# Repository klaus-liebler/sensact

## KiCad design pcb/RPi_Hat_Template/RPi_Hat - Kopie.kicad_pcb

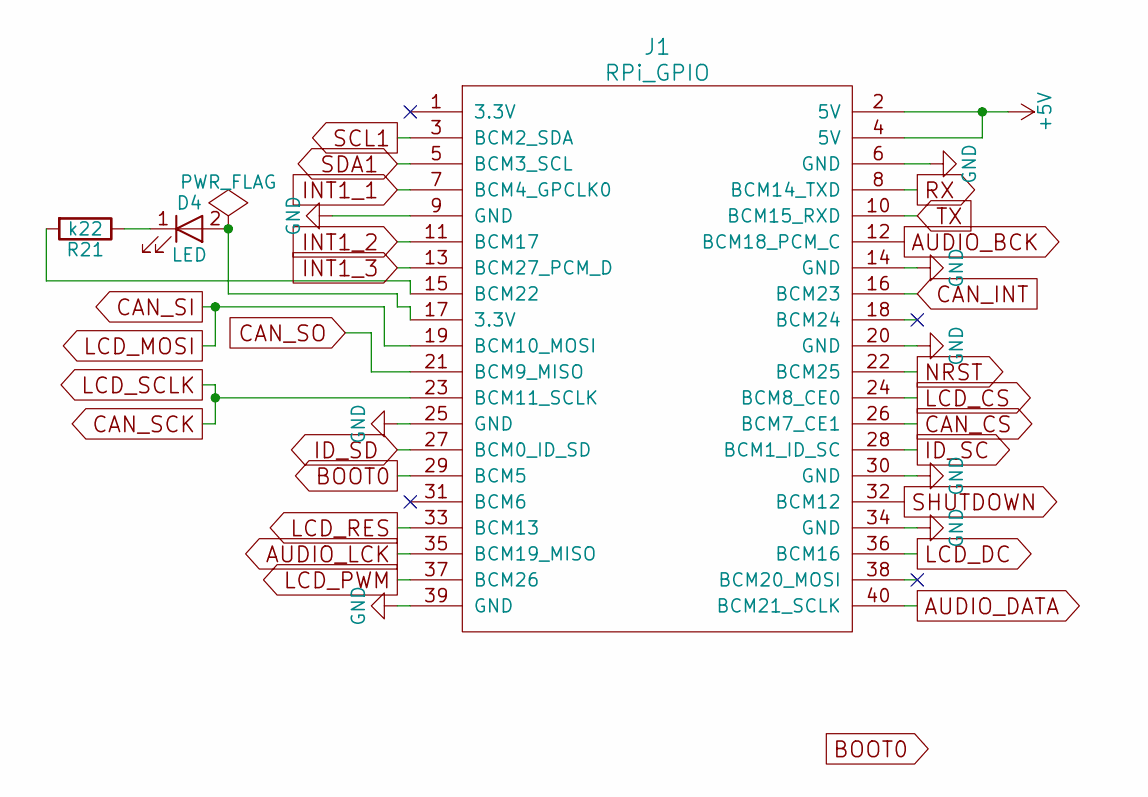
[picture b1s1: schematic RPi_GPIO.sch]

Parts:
D4: LED; LED_0805_handsolder
J1: RPi_GPIO; Pin_Header_Straight_2x20_Pitch2.54mm
R21: k22; R_0805_HandSoldering

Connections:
+5V: J1.2 (5V), J1.4 (5V); also elsewhere on the board
AUDIO_BCK: J1.12 (BCM18_PCM_C); also elsewhere on the board
AUDIO_DATA: J1.40 (BCM21_SCLK); also elsewhere on the board
AUDIO_LCK: J1.35 (BCM19_MISO); also elsewhere on the board
BOOT0: J1.29 (BCM5); also elsewhere on the board
CAN_CS: J1.26 (BCM7_CE1); also elsewhere on the board
CAN_INT: J1.16 (BCM23); also elsewhere on the board
CAN_SCK: J1.23 (BCM11_SCLK); also elsewhere on the board
CAN_SI: J1.19 (BCM10_MOSI); also elsewhere on the board
CAN_SO: J1.21 (BCM9_MISO); also elsewhere on the board
ID_SC: J1.28 (BCM1_ID_SC); also elsewhere on the board
ID_SD: J1.27 (BCM0_ID_SD); also elsewhere on the board
INT1_1: J1.7 (BCM4_GPCLK0); also elsewhere on the board
INT1_2: J1.11 (BCM17); also elsewhere on the board
INT1_3: J1.13 (BCM27_PCM_D); also elsewhere on the board
LCD_CS: J1.24 (BCM8_CE0); also elsewhere on the board
LCD_DC: J1.36 (BCM16); also elsewhere on the board
LCD_PWM: J1.37 (BCM26); also elsewhere on the board
LCD_RES: J1.33 (BCM13); also elsewhere on the board
NRST: J1.22 (BCM25); also elsewhere on the board
unnamed: D4.1 (K), R21.1
unnamed: D4.2 (A), J1.17 (3.3V)
unnamed: J1.15 (BCM22), R21.2
RX: J1.8 (BCM14_TXD); also elsewhere on the board
SCL1: J1.3 (BCM2_SDA); also elsewhere on the board
SDA1: J1.5 (BCM3_SCL); also elsewhere on the board
SHUTDOWN: J1.32 (BCM12); also elsewhere on the board
TX: J1.10 (BCM15_RXD); also elsewhere on the board

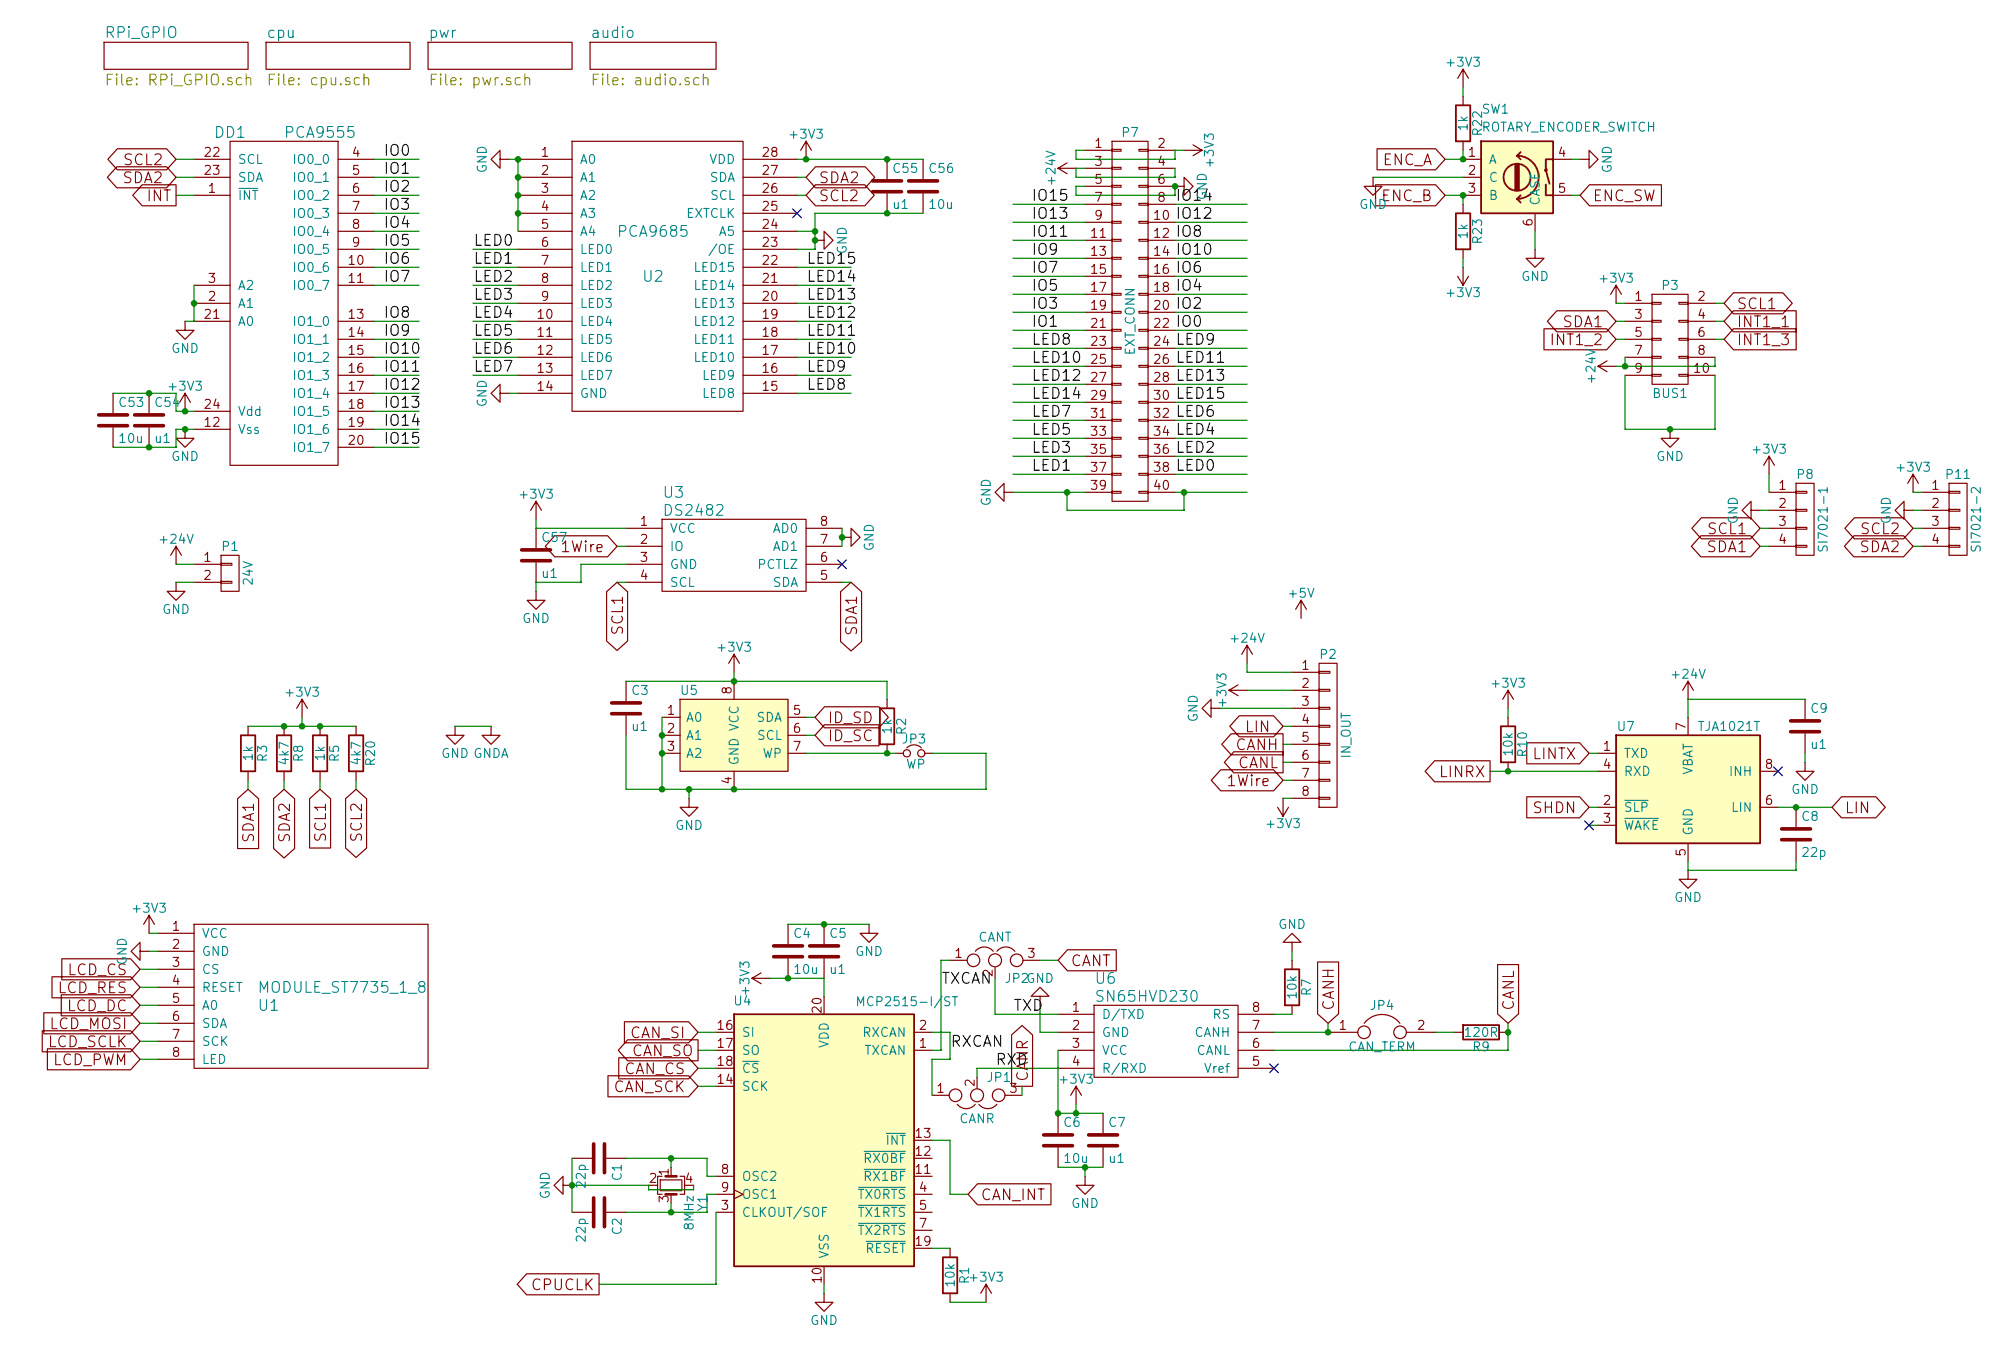
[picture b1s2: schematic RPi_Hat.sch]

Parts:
C1, C2, C8: 22p; C_0805_HandSoldering
C3, C5, C7, C9, C54, C55, C57: u1; C_0805_HandSoldering
C4, C6, C53, C56: 10u; C_1206_HandSoldering
DD1: PCA9555; TSSOP-24_4.4x7.8mm_Pitch0.65mm_handsolder
JP1: CANR; SMD-solder-bridge-3pin
JP2: CANT; SMD-solder-bridge-3pin
JP3: WP; SMD-solder-bridge
JP4: CAN_TERM; Pin_Header_Straight_1x02_Pitch2.54mm
P1: 24V; conn_2P
P2: IN_OUT; KF141R-8p
P3: BUS1; IDC-Header_2x05_Pitch2.54mm_Straight
P7: EXT_CONN; Pin_Header_Straight_2x20_Pitch2.54mm
P8: SI7021-1; MODULE_SI7021
P11: SI7021-2; MODULE_SI7021
R1, R7, R10: 10k; R_0805_HandSoldering
R2, R3, R5, R22, R23: 1k; R_0805_HandSoldering
R8, R20: 4k7; R_0805_HandSoldering
R9: 120R; R_1206_HandSoldering
SW1: ROTARY_ENCODER_SWITCH; encoder_alps-ec12d_case
U1: MODULE_ST7735_1_8; MODULE_ST7735_18
U2: PCA9685; TSSOP-28_4.4x9.7mm_Pitch0.65mm_handsolder
U3: DS2482; SOIC-8_3.9x4.9mm_Pitch1.27mm_handsolder
U4: MCP2515-I/ST; TSSOP-20_4.4x6.5mm_Pitch0.65mm_handsolder
U5: 24LC16; SOIC-8_3.9x4.9mm_Pitch1.27mm_handsolder
U6: SN65HVD230; SOIC-8_3.9x4.9mm_Pitch1.27mm_handsolder
U7: TJA1021T; SOIC-8_3.9x4.9mm_Pitch1.27mm_handsolder
Y1: 8MHz; quartz3225

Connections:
1Wire: P2.7, U3.2 (IO)
+3V3: C3.1, C4.2, C5.2, C6.1, C7.1, C53.1, C54.1, C55.1, C56.1, C57.1, DD1.24 (Vdd), P2.2, P2.8, P3.1, P7.1, P7.2, P8.1, P11.1, R1.2, R2.1, R3.1, R5.1, R8.1, R10.1, R20.1, R22.1, R23.2, U1.1 (VCC), U2.28 (VDD), U3.1 (VCC), U4.20 (VDD), U5.8 (VCC), U6.3 (VCC); also elsewhere on the board
+24V: C9.1, P1.1, P2.1, P3.7, P3.8, P7.3, P7.4, U7.7 (VBAT); also elsewhere on the board
/IO0: DD1.4 (IO0_0), P7.22
/IO1: DD1.5 (IO0_1), P7.21
/IO2: DD1.6 (IO0_2), P7.20
/IO3: DD1.7 (IO0_3), P7.19
/IO4: DD1.8 (IO0_4), P7.18
/IO5: DD1.9 (IO0_5), P7.17
/IO6: DD1.10 (IO0_6), P7.16
/IO7: DD1.11 (IO0_7), P7.15
/IO8: DD1.13 (IO1_0), P7.12
/IO9: DD1.14 (IO1_1), P7.13
/IO10: DD1.15 (IO1_2), P7.14
/IO11: DD1.16 (IO1_3), P7.11
/IO12: DD1.17 (IO1_4), P7.10
/IO13: DD1.18 (IO1_5), P7.9
/IO14: DD1.19 (IO1_6), P7.8
/IO15: DD1.20 (IO1_7), P7.7
/LED0: P7.38, U2.6 (LED0)
/LED1: P7.37, U2.7 (LED1)
/LED2: P7.36, U2.8 (LED2)
/LED3: P7.35, U2.9 (LED3)
/LED4: P7.34, U2.10 (LED4)
/LED5: P7.33, U2.11 (LED5)
/LED6: P7.32, U2.12 (LED6)
/LED7: P7.31, U2.13 (LED7)
/LED8: P7.23, U2.15 (LED8)
/LED9: P7.24, U2.16 (LED9)
/LED10: P7.25, U2.17 (LED10)
/LED11: P7.26, U2.18 (LED11)
/LED12: P7.27, U2.19 (LED12)
/LED13: P7.28, U2.20 (LED13)
/LED14: P7.29, U2.21 (LED14)
/LED15: P7.30, U2.22 (LED15)
/RXCAN: JP1.1, U4.2 (RXCAN)
/RXD: JP1.2, U6.4 (R/RXD)
/TXCAN: JP2.1, U4.1 (TXCAN)
/TXD: JP2.2, U6.1 (D/TXD)
CANH: JP4.1, P2.5, U6.7 (CANH)
CANL: P2.6, R9.1, U6.6 (CANL)
CANR: JP1.3; also elsewhere on the board
CANT: JP2.3; also elsewhere on the board
CAN_CS: U4.18 (~CS); also elsewhere on the board
CAN_INT: U4.13 (~INT); also elsewhere on the board
CAN_SCK: U1.7 (SCK), U4.14 (SCK); also elsewhere on the board
CAN_SI: U1.6 (SDA), U4.16 (SI); also elsewhere on the board
CAN_SO: U4.17 (SO); also elsewhere on the board
ENC_A: R22.2, SW1.1 (A); also elsewhere on the board
ENC_B: R23.1, SW1.3 (B); also elsewhere on the board
ENC_SW: SW1.5; also elsewhere on the board
ID_SC: U5.6 (SCL); also elsewhere on the board
ID_SD: U5.5 (SDA); also elsewhere on the board
INT: DD1.1 (~INT); also elsewhere on the board
INT1_1: P3.4; also elsewhere on the board
INT1_2: P3.5; also elsewhere on the board
INT1_3: P3.6; also elsewhere on the board
LCD_CS: U1.3 (CS); also elsewhere on the board
LCD_DC: U1.5 (A0); also elsewhere on the board
LCD_PWM: U1.8 (LED); also elsewhere on the board
LCD_RES: U1.4 (RESET); also elsewhere on the board
LIN: C8.1, P2.4, U7.6 (LIN)
LINRX: R10.2, U7.4 (RXD); also elsewhere on the board
LINTX: U7.1 (TXD); also elsewhere on the board
unnamed: C1.1, U4.8 (OSC2), Y1.1
unnamed: C2.1, U4.9 (OSC1), Y1.3
unnamed: JP3.1, R2.2, U5.7 (WP)
unnamed: JP4.2, R9.2
unnamed: R1.1, U4.19 (~RESET)
unnamed: R7.2, U6.8 (RS)
SCL1: P3.2, P8.3, R5.2, U3.4 (SCL); also elsewhere on the board
SCL2: DD1.22 (SCL), P11.3, R20.2, U2.26 (SCL); also elsewhere on the board
SDA1: P3.3, P8.4, R3.2, U3.5 (SDA); also elsewhere on the board
SDA2: DD1.23 (SDA), P11.4, R8.2, U2.27 (SDA); also elsewhere on the board
SHDN: U7.2 (~SLP~); also elsewhere on the board

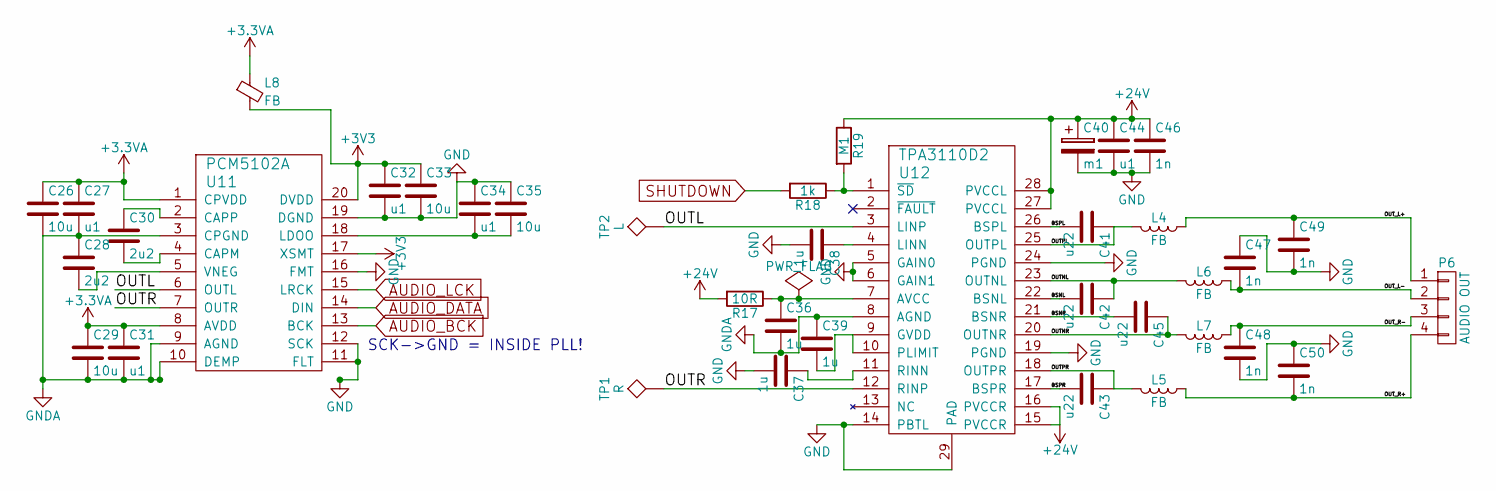
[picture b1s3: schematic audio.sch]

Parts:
C26, C29, C33, C35: 10u; C_1206_HandSoldering
C27, C31, C32, C34, C44: u1; C_0805_HandSoldering
C28, C30: 2u2; C_0805_HandSoldering
C36, C37, C38, C39: 1u; C_0805_HandSoldering
C40: m1; CP_Radial_D8.0mm_P3.50mm
C41, C42, C43, C45: u22; C_0805_HandSoldering
C46, C47, C48, C49, C50: 1n; C_0805_HandSoldering
L4, L5, L6, L7, L8: FB; C_1206_HandSoldering
P6: AUDIO OUT; mors_4p
R17: 10R; R_0805_HandSoldering
R18: 1k; R_0805_HandSoldering
R19: M1; R_0805_HandSoldering
TP1: R; Measurement_Point_Round-SMD-Pad_Small
TP2: L; Measurement_Point_Round-SMD-Pad_Small
U11: PCM5102A; TSSOP-20_4.4x6.5mm_Pitch0.65mm_handsolder
U12: TPA3110D2; TSSOP-28_4.4x9.7mm_Pitch0.65mm_pad_handsolder

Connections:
+3.3VA: C26.1, C27.1, C29.1, C31.1, L8.1, U11.1 (CPVDD), U11.8 (AVDD)
+3V3: C32.1, C33.1, L8.2, U11.17 (XSMT), U11.20 (DVDD); also elsewhere on the board
+24V: C40.1, C44.1, C46.1, R17.2, R19.1, U12.15 (PVCCR), U12.16 (PVCCR), U12.27 (PVCCL), U12.28 (PVCCL); also elsewhere on the board
/audio/BSNL: C42.2, U12.22 (BSNL)
/audio/BSNR: C45.2, U12.21 (BSNR)
/audio/BSPL: C41.2, U12.26 (BSPL)
/audio/BSPR: C43.2, U12.17 (BSPR)
/audio/OUTL: TP2.1, U11.6 (OUTL), U12.3 (LINP)
/audio/OUTNL: C42.1, L6.2, U12.23 (OUTNL)
/audio/OUTNR: C45.1, L7.2, U12.20 (OUTNR)
/audio/OUTPL: C41.1, L4.2, U12.25 (OUTPL)
/audio/OUTPR: C43.1, L5.2, U12.18 (OUTPR)
/audio/OUTR: TP1.1, U11.7 (OUTR), U12.12 (RINP)
/audio/OUT_L+: C49.1, L4.1, P6.1
/audio/OUT_L-: C47.2, L6.1, P6.2
/audio/OUT_R+: C50.2, L5.1, P6.4
/audio/OUT_R-: C48.1, L7.1, P6.3
AUDIO_BCK: U11.13 (BCK); also elsewhere on the board
AUDIO_DATA: U11.14 (DIN); also elsewhere on the board
AUDIO_LCK: U11.15 (LRCK); also elsewhere on the board
unnamed: C28.2, U11.5 (VNEG)
unnamed: C30.1, U11.2 (CAPP)
unnamed: C30.2, U11.4 (CAPM)
unnamed: C34.2, C35.2, U11.18 (LDOO)
unnamed: C36.1, R17.1, U12.7 (AVCC)
unnamed: C37.1, U12.11 (RINN)
unnamed: C38.1, U12.4 (LINN)
unnamed: C39.2, U12.9 (GVDD), U12.10 (PLIMIT)
unnamed: R18.1, R19.2, U12.1 (~SD)
SHUTDOWN: R18.2; also elsewhere on the board

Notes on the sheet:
SCK->GND = INSIDE PLL!

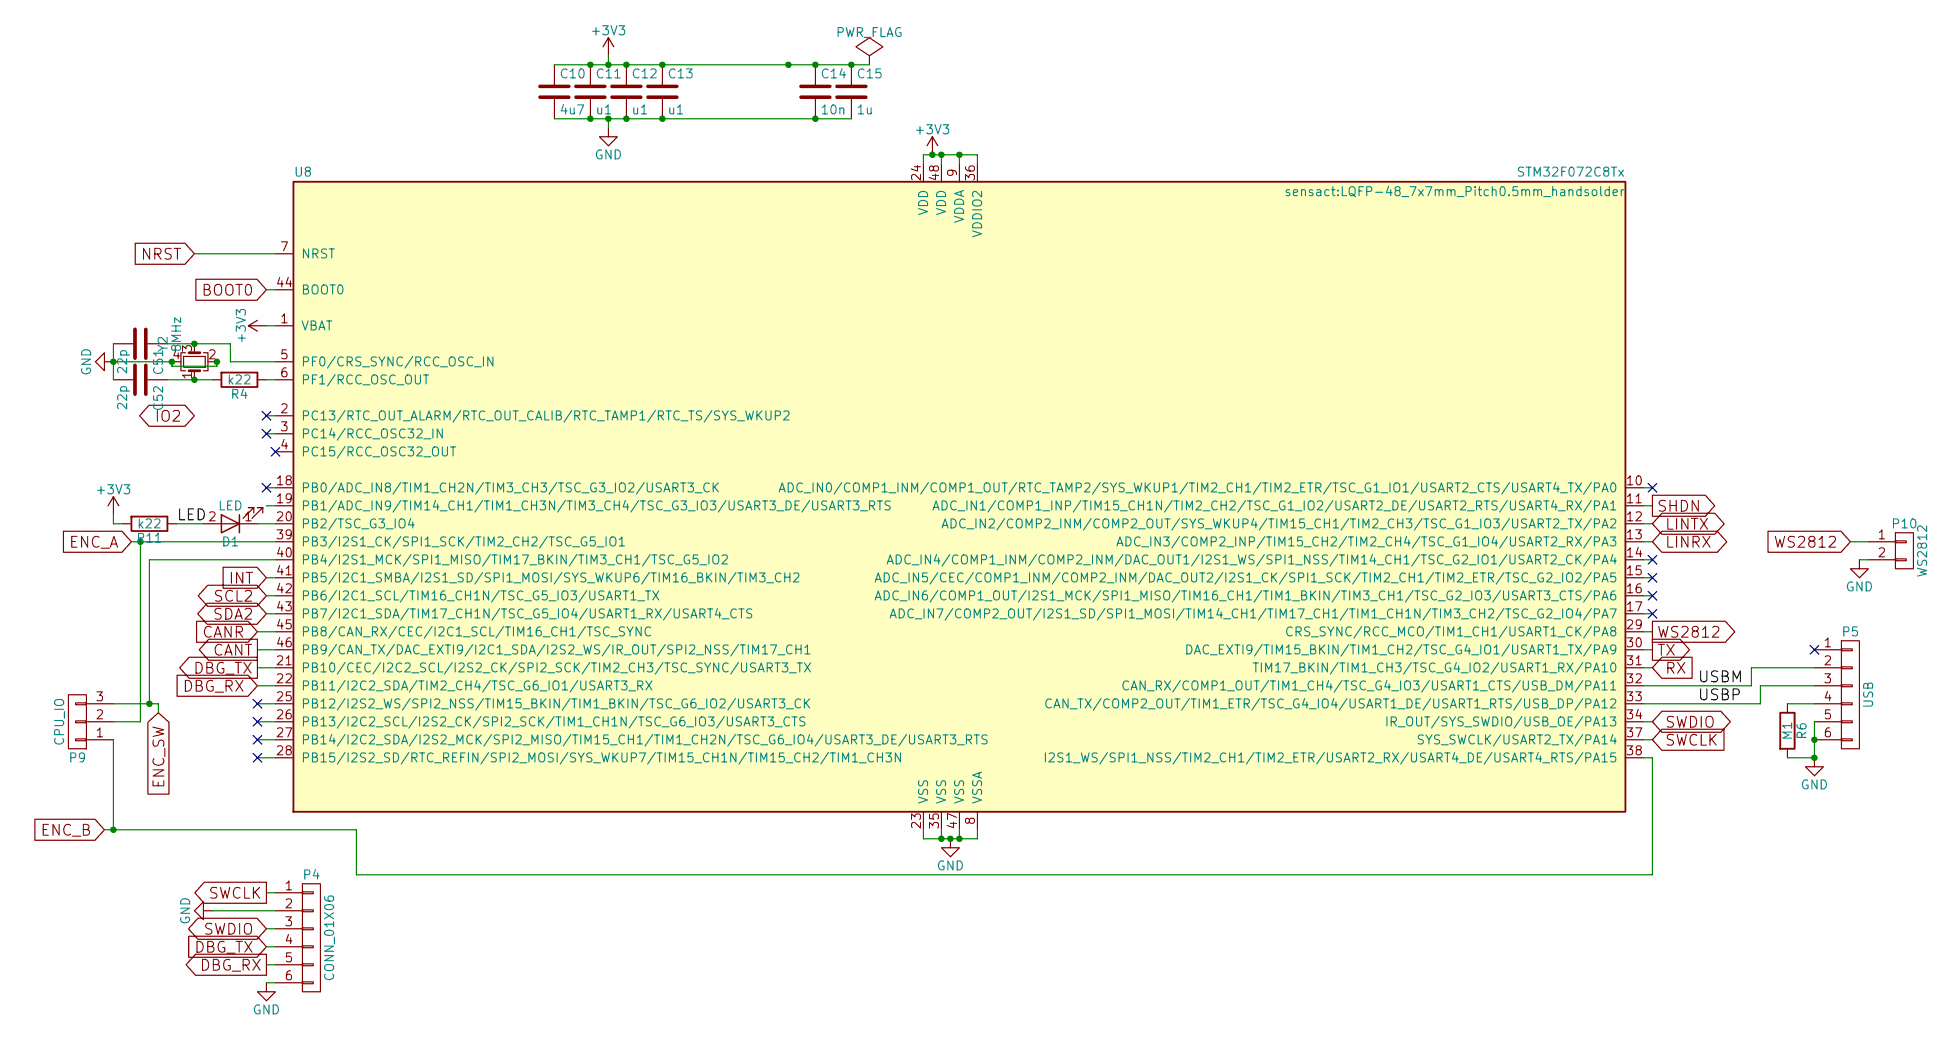
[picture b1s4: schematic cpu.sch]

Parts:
C10: 4u7; C_1206_HandSoldering
C11, C12, C13: u1; C_0805_HandSoldering
C14: 10n; C_0805_HandSoldering
C15: 1u; C_0805_HandSoldering
C51, C52: 22p; C_0805_HandSoldering
D1: LED; LED_0805_handsolder
P4: CONN_01X06; MicroUsbVertical
P5: USB; MicroUsbVertical
P9: CPU_IO; Pin_Header_Straight_1x03_Pitch2.54mm
P10: WS2812; Pin_Header_Straight_1x02_Pitch2.54mm
R4, R11: k22; R_0805_HandSoldering
R6: M1; R_0805_HandSoldering
U8: STM32F072C8Tx; LQFP-48_7x7mm_Pitch0.5mm_handsolder
Y2: 8MHz; quartz3225

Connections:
+3V3: C10.1, C11.1, C12.1, C13.1, C14.1, C15.1, P10.3, R11.2, U8.1 (VBAT), U8.9 (VDDA), U8.24 (VDD), U8.36 (VDDIO2), U8.48 (VDD); also elsewhere on the board
/cpu/LED: D1.2 (A), R11.1
/cpu/USBM: P5.2, U8.32 (CAN_RX/COMP1_OUT/TIM1_CH4/TSC_G4_IO3/US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)
/cpu/USBP: P5.3, U8.33 (CAN_TX/COMP2_OUT/TIM1_ETR/TSC_G4_IO4/US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)
BOOT0: U8.44 (BOOT0); also elsewhere on the board
CANR: U8.45 (PB8/CAN_RX/CEC/I2C1_SCL/TIM16_CH1/TSC_S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); also elsewhere on the board
CANT: U8.46 (PB9/CAN_TX/DAC_EXTI9/I2C1_SDA/I2S2_WS/I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); also elsewhere on the board
DBG_RX: P4.5, U8.22 (PB11/I2C2_SDA/TIM2_CH4/TSC_G6_IO1/USART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)
DBG_TX: P4.4, U8.21 (PB10/CEC/I2C2_SCL/I2S2_CK/SPI2_SCK/TIM2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)
ENC_A: P9.2, U8.39 (PB3/I2S1_CK/SPI1_SCK/TIM2_CH2/TSC_G5_IO1); also elsewhere on the board
ENC_B: P9.1, U8.38 (I2S1_WS/SPI1_NSS/TIM2_CH1/TIM2_ETR/USAR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); also elsewhere on the board
ENC_SW: P9.3, U8.40 (PB4/I2S1_MCK/SPI1_MISO/TIM17_BKIN/TIM3_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); also elsewhere on the board
INT: U8.41 (PB5/I2C1_SMBA/I2S1_SD/SPI1_MOSI/SYS_WKU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); also elsewhere on the board
LINRX: U8.13 (ADC_IN3/COMP2_INP/TIM15_CH2/TIM2_CH4/TS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); also elsewhere on the board
LINTX: U8.12 (ADC_IN2/COMP2_INM/COMP2_OUT/SYS_WKUP4/T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); also elsewhere on the board
NRST: U8.7 (NRST); also elsewhere on the board
unnamed: C51.1, U8.5 (PF0/CRS_SYNC/RCC_OSC_IN), Y2.3
unnamed: C52.1, R4.2, Y2.1
unnamed: D1.1 (K), U8.20 (PB2/TSC_G3_IO4)
unnamed: P5.4, R6.1
unnamed 113: U8.17 (ADC_IN7/COMP2_OUT/I2S1_SD/SPI1_MOSI/TIM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); also elsewhere on the board
unnamed 114: U8.16 (ADC_IN6/COMP1_OUT/I2S1_MCK/SPI1_MISO/TI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); also elsewhere on the board
unnamed 115: U8.15 (ADC_IN5/CEC/COMP1_INM/COMP2_INM/DAC_OUT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); also elsewhere on the board
unnamed 116: U8.14 (ADC_IN4/COMP1_INM/COMP2_INM/DAC_OUT1/I2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); also elsewhere on the board
unnamed: R4.1, U8.6 (PF1/RCC_OSC_OUT)
PB12: U8.25 (PB12/I2S2_WS/SPI2_NSS/TIM15_BKIN/TIM1_B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); also elsewhere on the board
PB14: U8.27 (PB14/I2C2_SDA/I2S2_MCK/SPI2_MISO/TIM15_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); also elsewhere on the board
PB15: U8.28 (PB15/I2S2_SD/RTC_REFIN/SPI2_MOSI/SYS_WK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); also elsewhere on the board
RX: U8.31 (TIM17_BKIN/TIM1_CH3/TSC_G4_IO2/USART1_R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); also elsewhere on the board
SCL2: U8.42 (PB6/I2C1_SCL/TIM16_CH1N/TSC_G5_IO3/USAR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); also elsewhere on the board
SDA2: U8.43 (PB7/I2C1_SDA/TIM17_CH1N/TSC_G5_IO4/USAR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); also elsewhere on the board
SHDN: U8.11 (ADC_IN1/COMP1_INP/TIM15_CH1N/TIM2_CH2/T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); also elsewhere on the board
SWCLK: P4.1, U8.37 (SYS_SWCLK/USART2_TX/PA14)
SWDIO: P4.3, U8.34 (IR_OUT/SYS_SWDIO/USB_OE/PA13)
TX: U8.30 (DAC_EXTI9/TIM15_BKIN/TIM1_CH2/TSC_G4_IO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); also elsewhere on the board
WS2812: P10.1, U8.29 (CRS_SYNC/RCC_MCO/TIM1_CH1/USART1_CK/PA8)

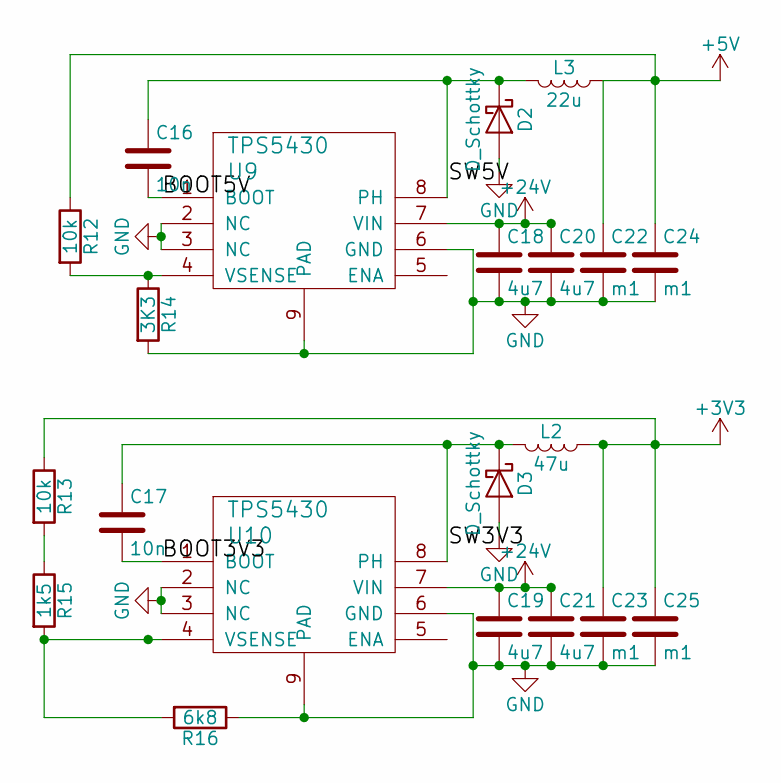
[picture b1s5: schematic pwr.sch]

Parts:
C16, C17: 10n; C_0805_HandSoldering
C18, C19, C20, C21: 4u7; C_1206_HandSoldering
C22, C23, C24, C25: m1; C_1206_HandSoldering
D2, D3: D_Schottky; do214aa_handsolder
L2: 47u; Inductor_CD104_handsolder
L3: 22u; Inductor_CD104_handsolder
R12, R13: 10k; R_0805_HandSoldering
R14: 3K3; R_0805_HandSoldering
R15: 1k5; R_0805_HandSoldering
R16: 6k8; R_0805_HandSoldering
U9, U10: TPS5430; SOIC-8_3.9x4.9mm_Pitch1.27mm_pad_handsolder

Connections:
+3V3: C23.1, C25.1, L2.1, R13.1; also elsewhere on the board
+5V: C22.1, C24.1, L3.1, R12.1; also elsewhere on the board
+24V: C18.1, C19.1, C20.1, C21.1, U9.7 (VIN), U10.7 (VIN); also elsewhere on the board
/pwr/BOOT3V3: C17.2, U10.1 (BOOT)
/pwr/BOOT5V: C16.2, U9.1 (BOOT)
/pwr/SW3V3: C17.1, D3.1 (K), L2.2, U10.8 (PH)
/pwr/SW5V: C16.1, D2.1 (K), L3.2, U9.8 (PH)
unnamed: R12.2, R14.1, U9.4 (VSENSE)
unnamed: R13.2, R15.1
unnamed: R15.2, R16.2, U10.4 (VSENSE)

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
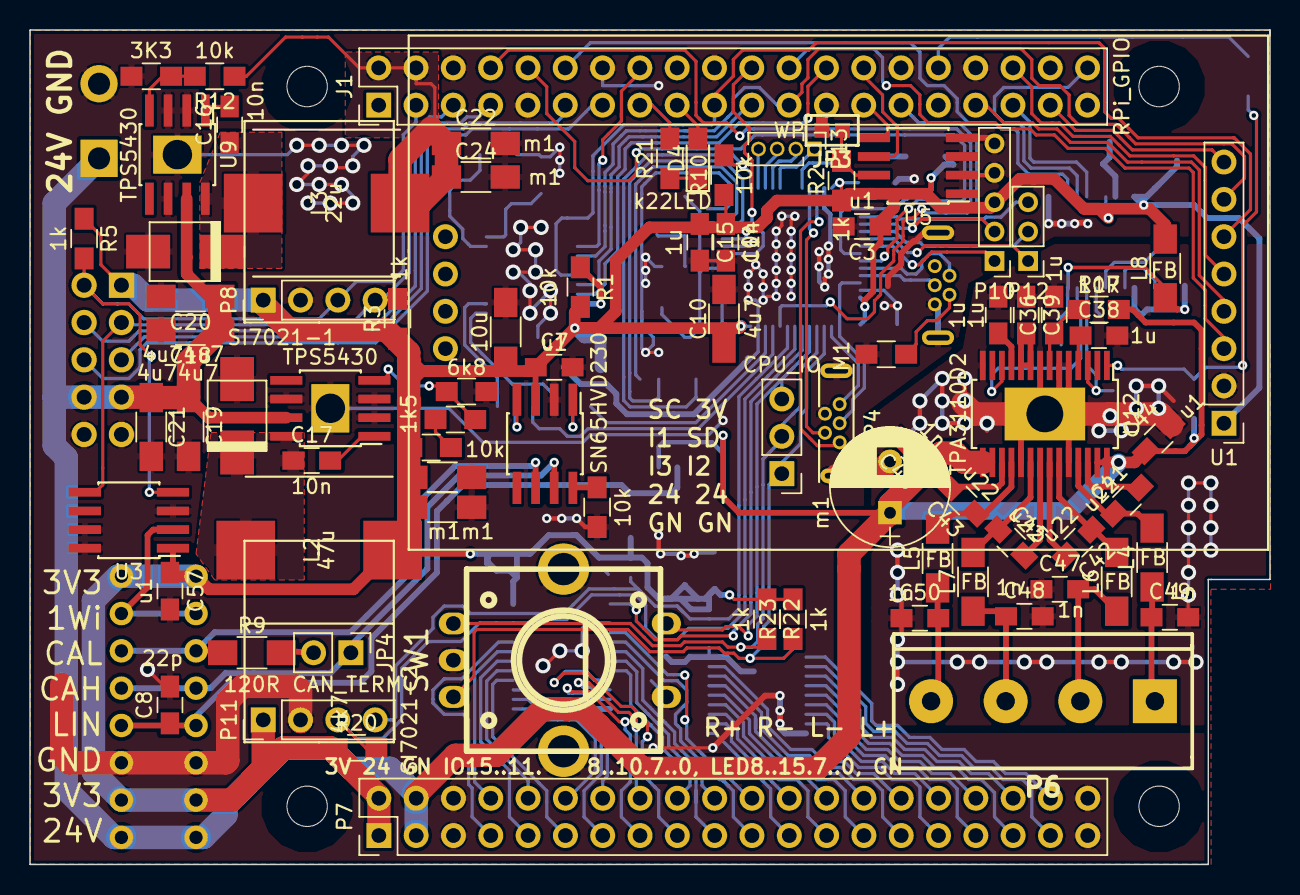
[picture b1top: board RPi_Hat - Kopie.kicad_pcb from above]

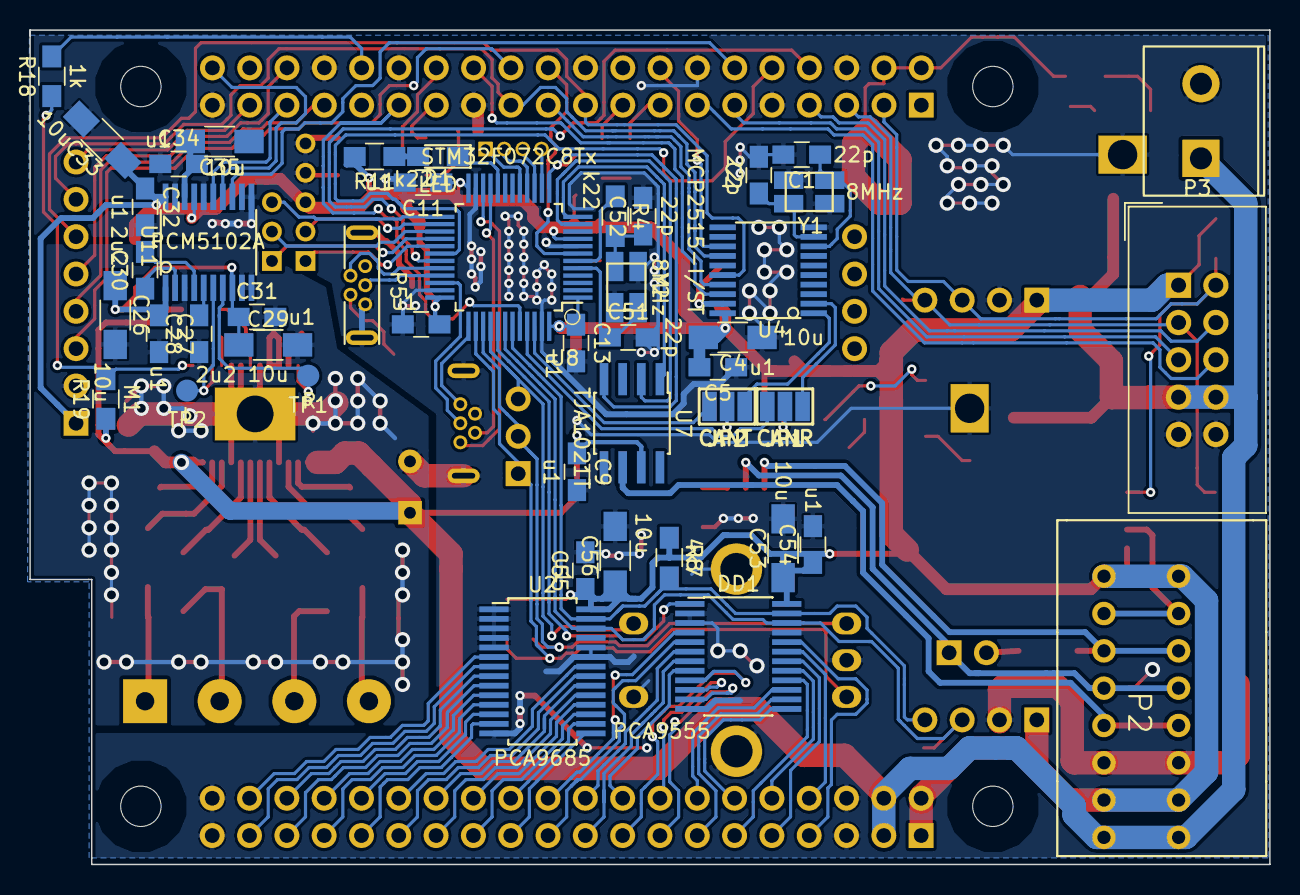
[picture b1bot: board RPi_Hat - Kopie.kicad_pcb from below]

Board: 2 copper layers, 84.4 x 56.8 mm, 127 parts (46 on the bottom side), 140 nets.

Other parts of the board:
P12: CONN_01X03; Pin_Header_Straight_1x03_Pitch2.00mm
P13: EXT; Pin_Header_Straight_1x04_Pitch1.27mm

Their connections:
unnamed 113: P13.1; also elsewhere on the board
unnamed 114: P13.2; also elsewhere on the board
unnamed 115: P13.3; also elsewhere on the board
unnamed 116: P13.4; also elsewhere on the board
PB12: P12.3; also elsewhere on the board
PB14: P12.2; also elsewhere on the board
PB15: P12.1; also elsewhere on the board

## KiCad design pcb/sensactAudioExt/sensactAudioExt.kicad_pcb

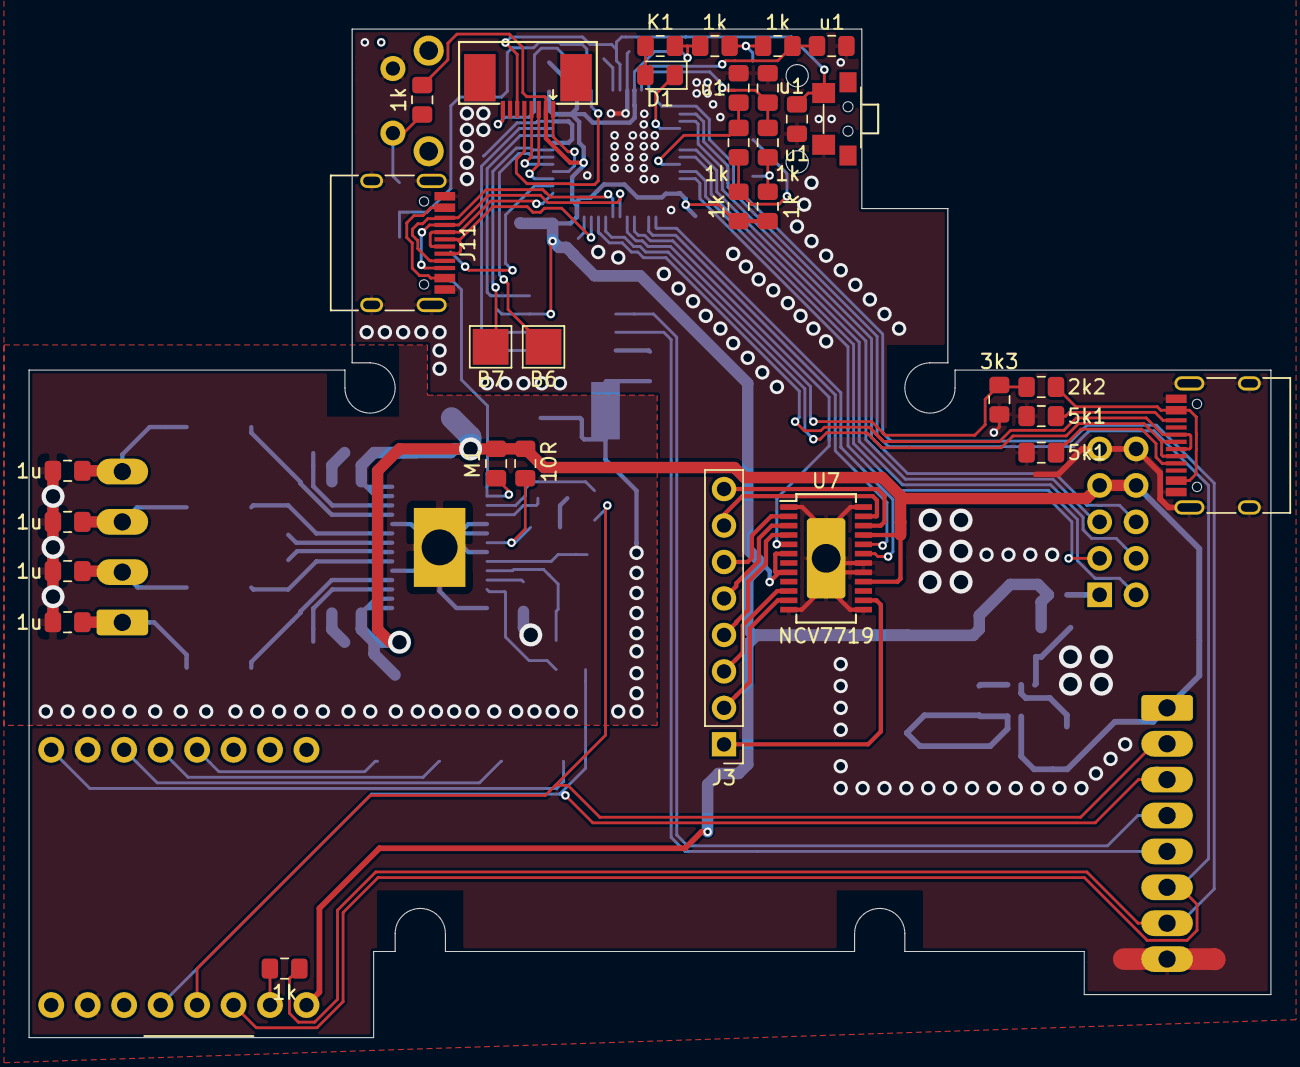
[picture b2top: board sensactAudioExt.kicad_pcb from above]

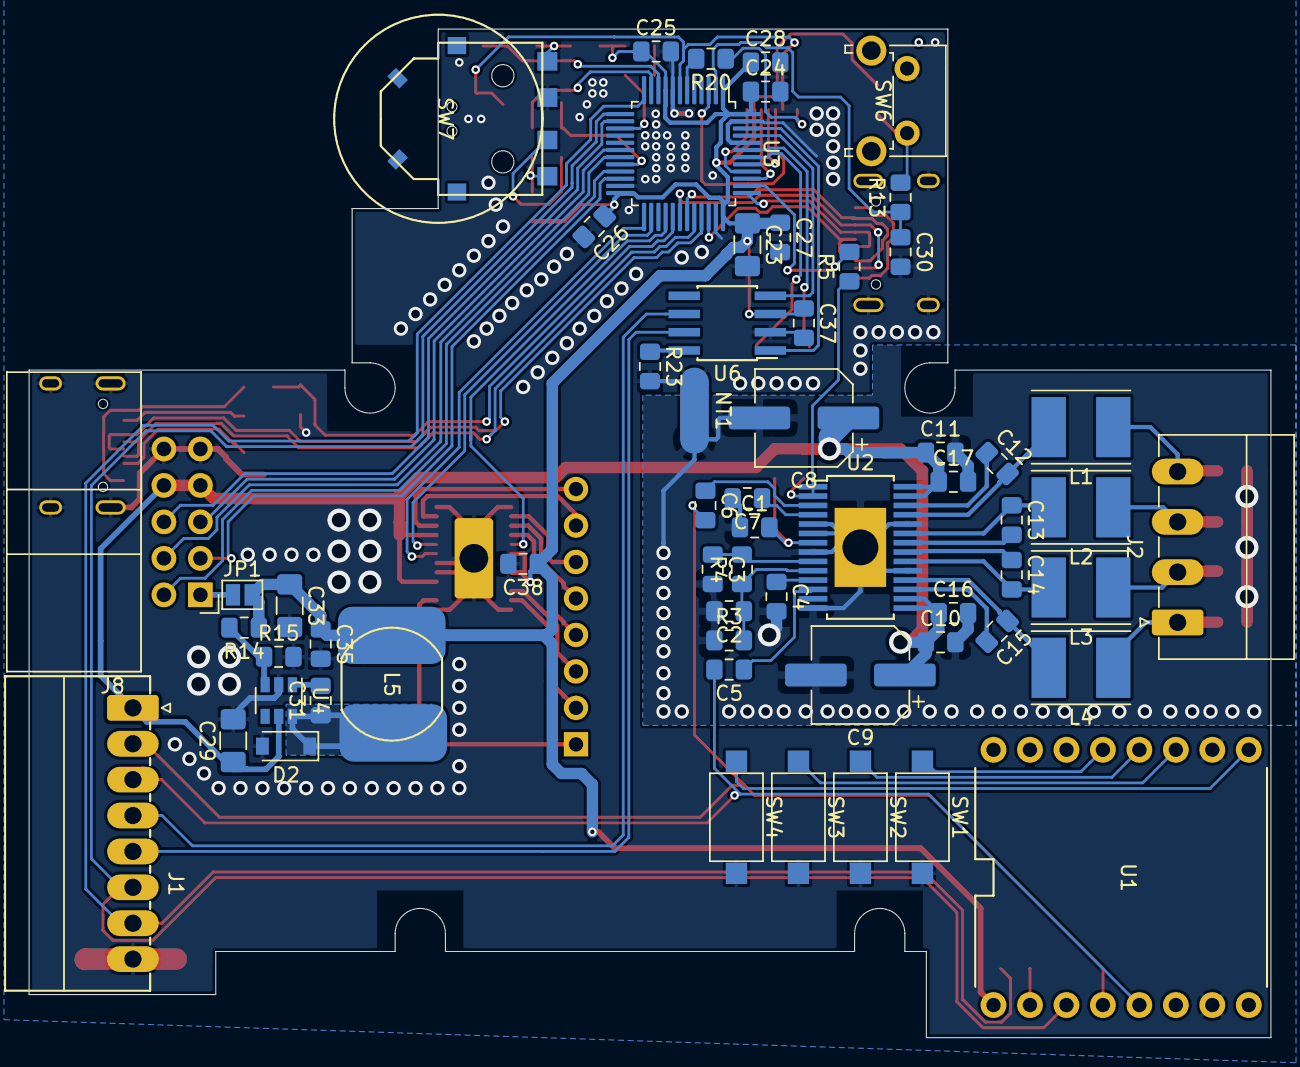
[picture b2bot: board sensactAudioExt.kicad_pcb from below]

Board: 2 copper layers, 86.5 x 70.2 mm, 92 parts (60 on the bottom side), 89 nets.

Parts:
C1, C2, C3, C4, C5, C6, C7, C18, C19, C20, C21: 1u; C_0805_2012Metric_Pad1.15x1.40mm_HandSolder
C8, C9: 100u; CP_Elec_6.3x7.7_HandSolder
C10, C11, C22, C24, C25, C26, C27, C28, C30, C31, C32, C34, C35, C36, C37, C38: u1; C_0805_2012Metric_Pad1.15x1.40mm_HandSolder
C12, C13, C14, C15: u22; C_0805_2012Metric_Pad1.15x1.40mm_HandSolder
C16, C17: 1n; C_0805_2012Metric_Pad1.15x1.40mm_HandSolder
C23, C29: 4u7; C_1206_3216Metric_Pad1.42x1.75mm_HandSolder
C33: m1; C_1206_3216Metric_Pad1.42x1.75mm_HandSolder
D1: LED; LED_0805_2012Metric_Pad1.15x1.40mm_HandSolder
D2: MBR0540; D_SOD-123
J1: Conn_01x08; PhoenixContact_MC_0,5_8-G-2.5_1x08_P2.50mm_Horizontal
J2: Audio Out; PhoenixContact_MC_1,5_4-G-3.5_1x04_P3.50mm_Horizontal
J3: Conn_01x08; PinHeader_1x08_P2.54mm_Vertical
J6: B6; TestPoint_Pad_2.5x2.5mm
J7: B7; TestPoint_Pad_2.5x2.5mm
J8: SensactBusConnector; IDC-Header_2x05_P2.54mm_Horizontal
J11, J12: USB_C_Receptacle_USB2.0; USB_C_Receptacle_HRO_TYPE-C-31-M-12
JP1: 3V3_INT; SolderJumper-2_P1.3mm_Open_Pad1.0x1.5mm
L1, L2, L3, L4: 33u; L_Taiyo-Yuden_NR-50xx_HandSoldering
L5: 150u; Inductor_CD75_handsolder
NT1: Net-Tie_2; NetTie-2_SMD_Pad2.0mm
R1, R5, R12, R13, R15, R16, R17, R18, R19, R21, R22: 1k; R_0805_2012Metric_Pad1.15x1.40mm_HandSolder
R2: 10R; R_0805_2012Metric_Pad1.15x1.40mm_HandSolder
R3, R4, R23: 10k; R_0805_2012Metric_Pad1.15x1.40mm_HandSolder
R6: M1; R_0805_2012Metric_Pad1.15x1.40mm_HandSolder
R7: K1; R_0805_2012Metric_Pad1.15x1.40mm_HandSolder
R8, R14: 3k3; R_0805_2012Metric_Pad1.15x1.40mm_HandSolder
R9: 2k2; R_0805_2012Metric_Pad1.15x1.40mm_HandSolder
R10, R11: 5k1; R_0805_2012Metric_Pad1.15x1.40mm_HandSolder
R20: 10r; R_0805_2012Metric_Pad1.15x1.40mm_HandSolder
SW1, SW2, SW3, SW4: SW_Push; SW_SPST_CK_RS282G05A3
SW5: Reset; SW_SPST_2x4x3,5
SW6: SW_Push; SW_Tactile_SPST_Angled_PTS645Vx83-2LFS
SW7: Mitsumi_SIQ-02FVS3
U1: DFPlayerMini
U2: TPA3110D2; TSSOP-28_4.4x9.7mm_Pitch0.65mm_pad_handsolder
U3: STM32F072C8Tx; LQFP-48_7x7mm_P0.5mm_handsolder
U4: LMR14206; SOT-23-6
U5: FP-096H09A; FPC_TOP_1x08-1MP_P0.50mm_Horizontal
U6: SN65HVD230; SOIC-8_3.9x4.9mm_Pitch1.27mm_handsolder
U7: NCV7719; SSOP-24_3.9x8.7mm_P0.65mm_EP2.7x5.6mm

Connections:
+3V3: C23.1, C24.1, C25.1, C26.1, C27.1, C28.1, C33.1, C35.1, C37.1, C38.1, JP1.2, L5.1, R7.1, R12.1, R14.1, R18.1, R19.2, R21.1, U1.1, U3.1, U3.9, U3.24, U3.36, U3.48, U5.2, U6.3, U7.6, U7.8
+24V: C8.1, C9.1, C10.1, C11.1, C16.1, C17.1, C29.1, J1.1, J8.7, J8.8, R2.1, R6.1, U2.15, U2.16, U2.27, U2.28, U4.5, U7.16, U7.21
/DAC_L: C5.2, J1.3, U1.5
/DAC_R: C6.2, J1.2, U1.4
/hmi/CB: C31.2, U4.1
/hmi/FB: R14.2, R15.1, U4.3
/hmi/INT0: J8.4, U3.19
/hmi/INT1: J8.5, U3.18
/hmi/INT2: J8.6, U3.14
/hmi/NRST: C22.1, SW5.1, U3.7, U5.6
/hmi/RX: J11.A8, J11.B8, U3.31
/hmi/SCL: J8.2, U3.21
/hmi/SDA: J8.3, U3.22
/hmi/SW: C31.1, D2.1, L5.2, U4.6
/hmi/SWCLK: J11.A7, J11.B7, U3.37
/hmi/SWDIO: J11.A6, J11.B6, U3.34
/hmi/TX: J11.A5, J11.B5, U3.30
/hmi/USB+: J12.A6, J12.B6, U3.33
/hmi/USB-: J12.A7, J12.B7, U3.32
AUDIO_SHUTDOWN: R5.2, U3.38
CANH: J1.5, U6.7
CANL: J1.4, U6.6
CANR: U3.45, U6.4
CANT: U3.46, U6.1
GND: C22.2, C23.2, C24.2, C25.2, C26.2, C27.2, C28.2, C29.2, C30.2, C32.1, C33.2, C34.2, C35.2, C36.2, C37.2, C38.2, D2.2, J1.8, J8.9, J8.10, J11.A1, J11.A12, J11.B1, J11.B12, J11.S1, J12.A1, J12.A12, J12.B1, J12.B12, J12.S1, NT1.1, R8.1, R10.1, R11.1, R15.2, R23.2, SW1.2, SW2.2, SW3.2, SW4.2, SW5.2, SW6.1, SW7.C, U1.7, U1.10, U3.8, U3.23, U3.35, U3.44, U3.47, U4.2, U5.7, U6.2, U7.1, U7.12, U7.13, U7.17, U7.18, U7.24, U7.25
GNDA: C1.1, C2.2, C3.2, C4.2, C7.2, C8.2, C9.2, C10.2, C11.2, C16.2, C17.2, C18.1, C19.1, C20.1, C21.1, NT1.2, R3.1, U2.5, U2.6, U2.8, U2.14, U2.19, U2.24, U2.29
LCDBL: R20.2, U3.6
LCDCS: U3.40, U5.1
LCDRS: U3.3, U5.5
LED: D1.1, U3.15
MP3RX: J1.7, R1.2, U3.12
MP3TX: J1.6, U1.3, U3.13
unnamed: C1.2, R2.2, U2.7
unnamed: C2.1, R3.2, R4.1, U2.10
unnamed: C3.1, R4.2, U2.9
unnamed: C4.1, U2.11
unnamed: C5.1, U2.12
unnamed: C6.1, U2.3
unnamed: C7.1, U2.4
unnamed: C12.1, U2.26
unnamed: C12.2, L1.2, U2.25
unnamed: C13.1, L2.2, U2.23
unnamed: C13.2, U2.22
unnamed: C14.1, U2.21
unnamed: C14.2, L3.2, U2.20
unnamed: C15.1, L4.2, U2.18
unnamed: C15.2, U2.17
unnamed: C18.2, J2.4, L1.1
unnamed: C19.2, J2.3, L2.1
unnamed: C20.2, J2.2, L3.1
unnamed: C21.2, J2.1, L4.1
unnamed: D1.2, R7.2
unnamed: J3.1, U7.14
unnamed: J3.2, U7.11
unnamed: J3.3, U7.10
unnamed: J3.4, U7.4
unnamed: J3.5, U7.3
unnamed: J3.6, U7.2
unnamed: J3.7, U7.23
unnamed: J3.8, U7.22
unnamed: J6.1, U3.42
unnamed: J7.1, U3.43
unnamed: J8.1, JP1.1
unnamed: J11.A4, J11.A9, J11.B4, J11.B9
unnamed: J12.A4, J12.A9, J12.B4, J12.B9, R9.2
unnamed: J12.A5, R10.2
unnamed: J12.B5, R11.2
unnamed: R1.1, U1.2
unnamed: R5.1, R6.2, U2.1, U2.2
unnamed: R12.2, R13.2, SW6.2
unnamed: R16.1, R18.2, SW7.A
unnamed: R17.1, R19.1, SW7.B
unnamed: R20.1, U5.8
unnamed: R21.2, R22.2, SW7.S
unnamed: R23.1, U6.8
unnamed: SW1.1, U1.13
unnamed: SW2.1, U1.12
unnamed: SW3.1, U1.11
unnamed: SW4.1, U1.9
ROTA: C32.2, R16.2, U3.11
ROTB: C34.1, R17.2, U3.10
ROTS: C36.1, R22.1, U3.20
S: C30.1, R13.1, U3.2
SPI2_CLK: U3.26, U7.20
SPI2_CS: U3.25, U7.19
SPI2_MOSI: U3.28, U7.5
SPI_CLK: U3.39, U5.3
SPI_MOSI: U3.41, U5.4
VBUS: R8.2, R9.1, U3.29
